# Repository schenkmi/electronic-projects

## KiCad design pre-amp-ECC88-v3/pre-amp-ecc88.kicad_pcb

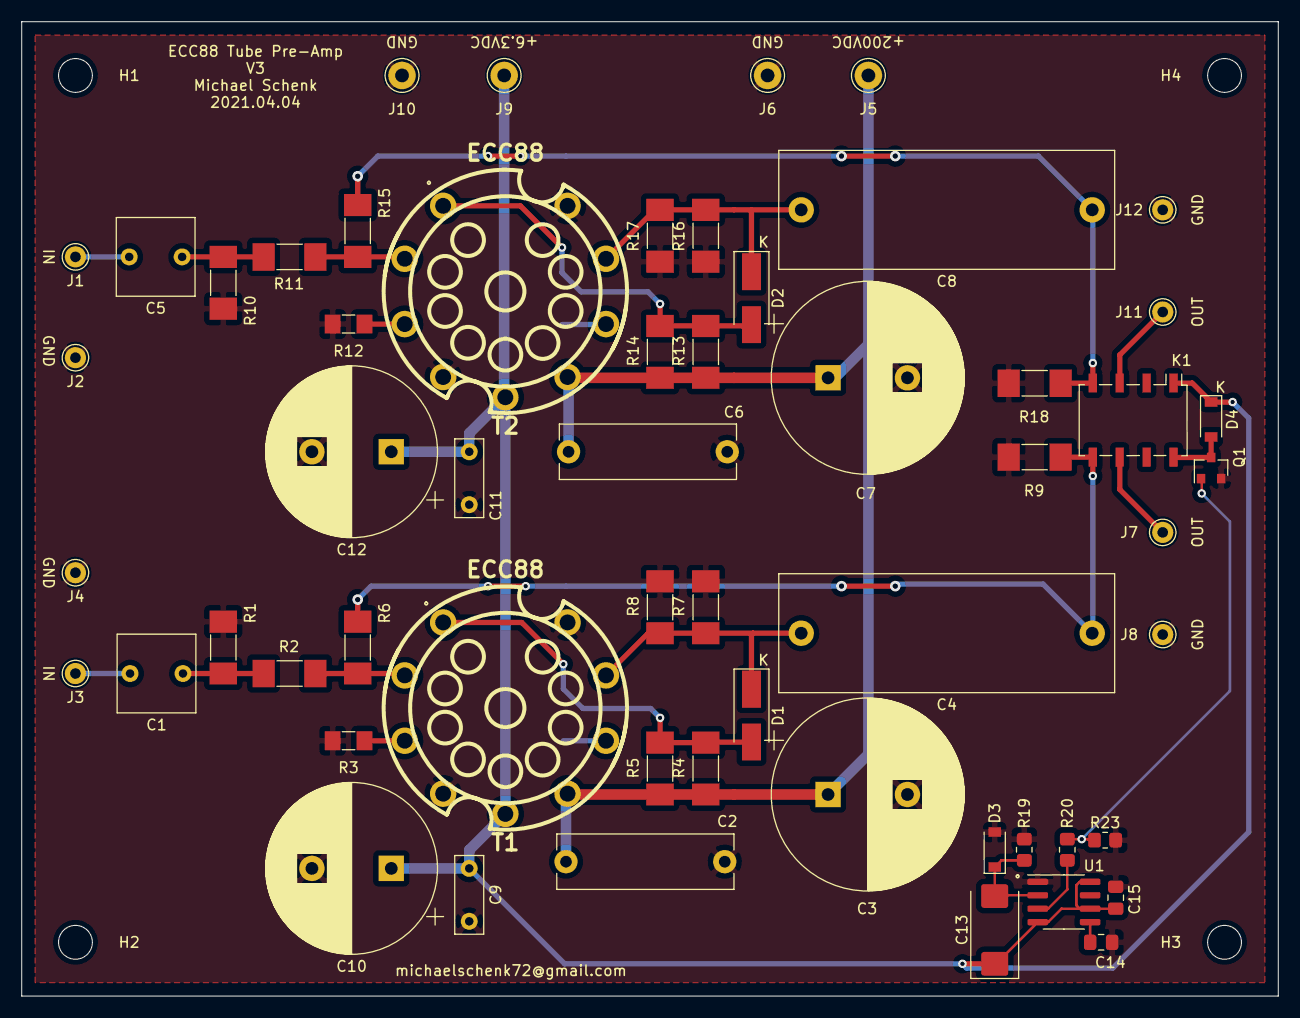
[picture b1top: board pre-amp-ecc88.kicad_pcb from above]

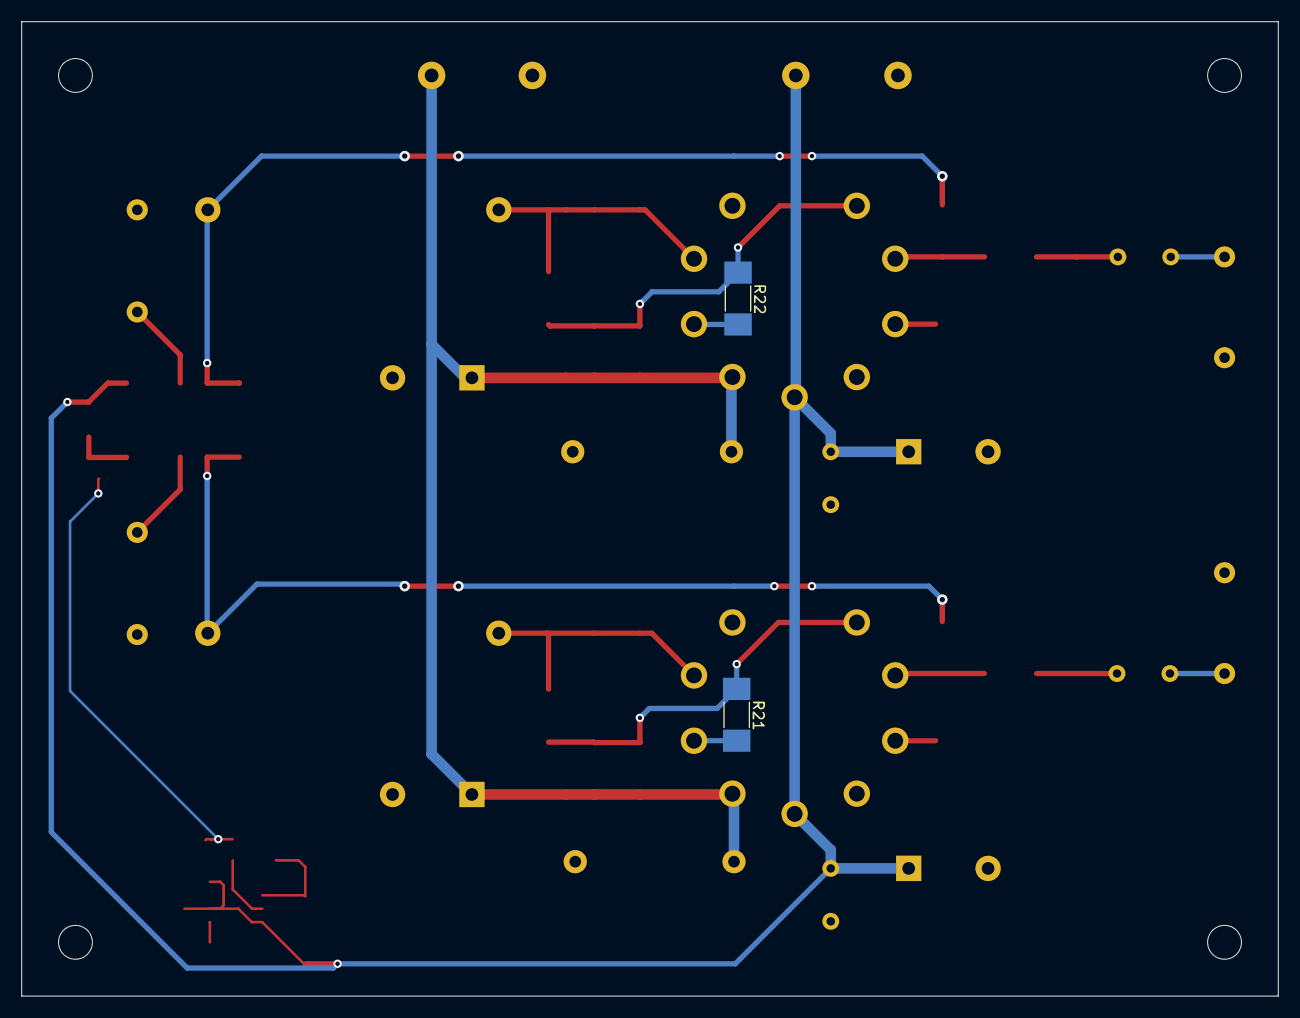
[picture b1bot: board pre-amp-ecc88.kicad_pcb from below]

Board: 2 copper layers, 118.7 x 92.1 mm, 63 parts (2 on the bottom side), 26 nets.

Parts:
C1, C5: 3.3uF; C_Rect_L7.2mm_W7.2mm_P5.00mm_FKS2_FKP2_MKS2_MKP2
C2, C6: 100nF; C_Rect_L16.5mm_W5.0mm_P15.00mm_MKT
C3, C7: 100uF; CP_Radial_D18.0mm_P7.50mm
C4, C8: 2.2uF; C_Rect_L31.5mm_W11.0mm_P27.50mm_MKS4
C9, C11: 100nF; C_Rect_L7.2mm_W2.5mm_P5.00mm_FKS2_FKP2_MKS2_MKP2
C10, C12: 2200uF; CP_Radial_D16.0mm_P7.50mm
C13: 15uF/25V; CP_EIA-7343-31_Kemet-D_Pad2.25x2.55mm_HandSolder
C14, C15: 100nF/50V; C_0805_2012Metric_Pad1.18x1.45mm_HandSolder
D1, D2: 1N4007; D_SMA_Handsoldering
D3, D4: 1N4148W; D_SOD-123
H1, H2, H3, H4: MountingHole; MountingHole_3.2mm_M3
J1, J2, J3, J4, J7, J8, J11, J12: Conn_01x01; Pin_D1.0mm_L10.0mm
J5, J6, J9, J10: Conn_01x01; Pin_D1.3mm_L11.0mm
K1: G6K-2; Relay_DPDT_Omron_G6K-2F
Q1: MMBT3904; SOT-23
R1, R9, R10, R18: 1Meg; R_MELF_MMB-0207
R2, R11: 47k; R_MELF_MMB-0207
R3, R12: 1.21k; R_MiniMELF_MMA-0204
R4, R7, R13, R16: 56k; R_MELF_MMB-0207
R5, R8, R14, R17: 39k; R_MELF_MMB-0207
R6, R15: 100k; R_MELF_MMB-0207
R19: 2Meg; R_0805_2012Metric_Pad1.20x1.40mm_HandSolder
R20, R23: 2.49k; R_0805_2012Metric_Pad1.20x1.40mm_HandSolder
R21, R22: 100R; R_MELF_MMB-0207
T1, T2: ECC88; TubeNoval-ECC88
U1: TLC555xD; SOIC-8_3.9x4.9mm_P1.27mm

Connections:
GND: C2.2, C3.2, C6.2, C7.2, C9.2, C10.2, C11.2, C12.2, C14.2, C15.2, D3.2, J2.1, J4.1, J6.1, J8.1, J10.1, J12.1, Q1.2, R1.2, R3.2, R7.2, R8.2, R9.2, R10.2, R12.2, R16.2, R17.2, R18.2, R19.2, R23.2, T1.4, T1.9, T2.4, T2.9, U1.1
unnamed: C1.1, R1.1, R2.2
unnamed: C1.2, J3.1
unnamed: C4.1, K1.5, R6.1, R9.1
unnamed: C4.2, D1.1, R7.1, R8.1, T1.8
unnamed: C5.1, R10.1, R11.2
unnamed: C5.2, J1.1
unnamed: C8.1, K1.4, R15.1, R18.1
unnamed: C8.2, D2.1, R16.1, R17.1, T2.8
unnamed: C13.2, D3.1, R19.1, U1.2
unnamed: C14.1, U1.5
unnamed: D1.2, R4.2, R5.2, R21.1, T1.1
unnamed: D2.2, R13.2, R14.2, R22.1, T2.1
unnamed: D4.2, K1.8, Q1.3
unnamed: J7.1, K1.6
unnamed: J11.1, K1.3
unnamed: Q1.1, R20.1, R23.1
unnamed: R2.1, R6.2, T1.2
unnamed: R3.1, T1.3
unnamed: R11.1, R15.2, T2.2
unnamed: R12.1, T2.3
unnamed: R20.2, U1.3
unnamed: R21.2, T1.7
unnamed: R22.2, T2.7
VDDA: C2.1, C3.1, C6.1, C7.1, J5.1, R4.1, R5.1, R13.1, R14.1, T1.6, T2.6
VDDF: C9.1, C10.1, C11.1, C12.1, C13.1, C15.1, D4.1, J9.1, K1.1, T1.5, T2.5, U1.4, U1.6, U1.8
